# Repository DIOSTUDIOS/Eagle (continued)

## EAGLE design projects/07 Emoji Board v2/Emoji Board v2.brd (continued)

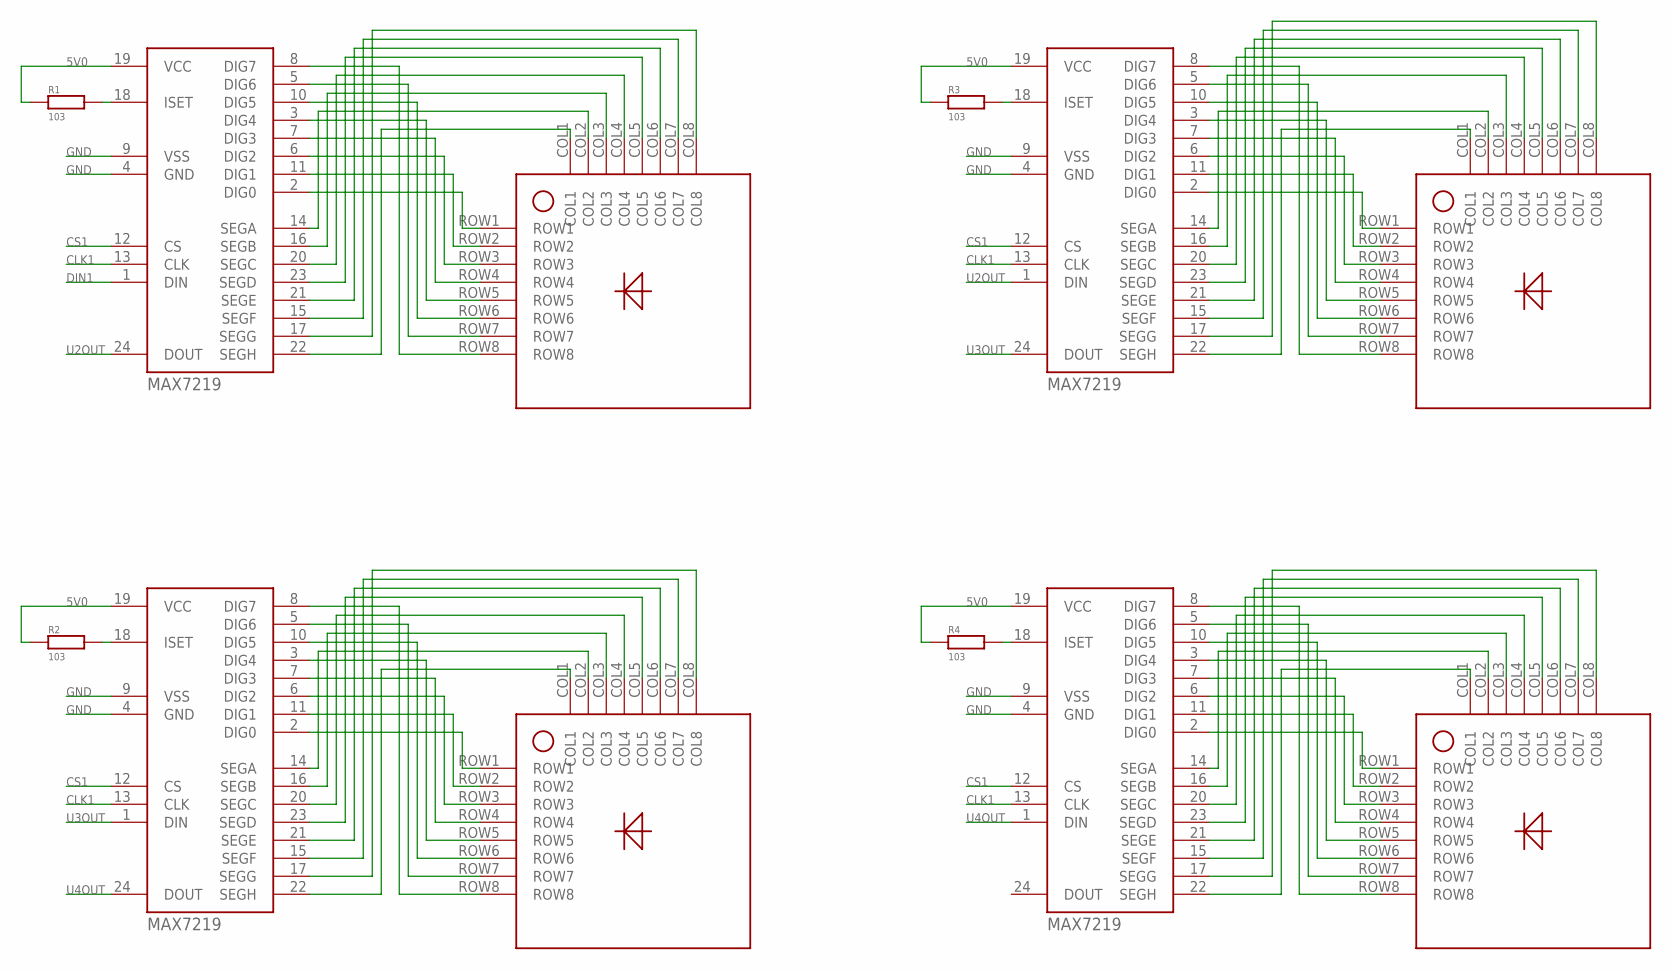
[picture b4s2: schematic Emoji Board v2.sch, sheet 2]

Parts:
R1, R2, R3, R4: 103; R0805
T1, T2, T3, T4: DOT-MATRIX-AS; 1088AS
U2, U3, U4, U5: MAX7219; SOP24

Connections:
5V0: R1.1, R2.1, R3.1, R4.1, U2.19 (VCC), U3.19 (VCC), U4.19 (VCC), U5.19 (VCC); also elsewhere on the board
CLK1: U2.13 (CLK), U3.13 (CLK), U4.13 (CLK), U5.13 (CLK); also elsewhere on the board
CS1: U2.12 (CS), U3.12 (CS), U4.12 (CS), U5.12 (CS); also elsewhere on the board
DIN1: U2.1 (DIN); also elsewhere on the board
GND: U2.4 (GND), U2.9 (VSS), U3.4 (GND), U3.9 (VSS), U4.4 (GND), U4.9 (VSS), U5.4 (GND), U5.9 (VSS); also elsewhere on the board
unnamed: T1.ROW1, U2.2 (DIG0)
unnamed: T1.ROW2, U2.11 (DIG1)
unnamed: T1.ROW3, U2.6 (DIG2)
unnamed: T1.ROW4, U2.7 (DIG3)
unnamed: T1.ROW5, U2.3 (DIG4)
unnamed: T1.ROW6, U2.10 (DIG5)
unnamed: T1.ROW7, U2.5 (DIG6)
unnamed: T1.ROW8, U2.8 (DIG7)
unnamed: T1.COL1, U2.22 (SEGH)
unnamed: T1.COL2, U2.14 (SEGA)
unnamed: T1.COL3, U2.16 (SEGB)
unnamed: T1.COL4, U2.20 (SEGC)
unnamed: T1.COL5, U2.23 (SEGD)
unnamed: T1.COL6, U2.21 (SEGE)
unnamed: T1.COL7, U2.15 (SEGF)
unnamed: T1.COL8, U2.17 (SEGG)
unnamed: T2.ROW1, U3.2 (DIG0)
unnamed: T2.ROW2, U3.11 (DIG1)
unnamed: T2.ROW3, U3.6 (DIG2)
unnamed: T2.ROW4, U3.7 (DIG3)
unnamed: T2.ROW5, U3.3 (DIG4)
unnamed: T2.ROW6, U3.10 (DIG5)
unnamed: T2.ROW7, U3.5 (DIG6)
unnamed: T2.ROW8, U3.8 (DIG7)
unnamed: T2.COL1, U3.22 (SEGH)
unnamed: T2.COL2, U3.14 (SEGA)
unnamed: T2.COL3, U3.16 (SEGB)
unnamed: T2.COL4, U3.20 (SEGC)
unnamed: T2.COL5, U3.23 (SEGD)
unnamed: T2.COL6, U3.21 (SEGE)
unnamed: T2.COL7, U3.15 (SEGF)
unnamed: T2.COL8, U3.17 (SEGG)
unnamed: T3.ROW1, U4.2 (DIG0)
unnamed: T3.ROW2, U4.11 (DIG1)
unnamed: T3.ROW3, U4.6 (DIG2)
unnamed: T3.ROW4, U4.7 (DIG3)
unnamed: T3.ROW5, U4.3 (DIG4)
unnamed: T3.ROW6, U4.10 (DIG5)
unnamed: T3.ROW7, U4.5 (DIG6)
unnamed: T3.ROW8, U4.8 (DIG7)
unnamed: T3.COL1, U4.22 (SEGH)
unnamed: T3.COL2, U4.14 (SEGA)
unnamed: T3.COL3, U4.16 (SEGB)
unnamed: T3.COL4, U4.20 (SEGC)
unnamed: T3.COL5, U4.23 (SEGD)
unnamed: T3.COL6, U4.21 (SEGE)
unnamed: T3.COL7, U4.15 (SEGF)
unnamed: T3.COL8, U4.17 (SEGG)
unnamed: T4.ROW1, U5.2 (DIG0)
unnamed: T4.ROW2, U5.11 (DIG1)
unnamed: T4.ROW3, U5.6 (DIG2)
unnamed: T4.ROW4, U5.7 (DIG3)
unnamed: T4.ROW5, U5.3 (DIG4)
unnamed: T4.ROW6, U5.10 (DIG5)
unnamed: T4.ROW7, U5.5 (DIG6)
unnamed: T4.ROW8, U5.8 (DIG7)
unnamed: T4.COL1, U5.22 (SEGH)
unnamed: T4.COL2, U5.14 (SEGA)
unnamed: T4.COL3, U5.16 (SEGB)
unnamed: T4.COL4, U5.20 (SEGC)
unnamed: T4.COL5, U5.23 (SEGD)
unnamed: T4.COL6, U5.21 (SEGE)
unnamed: T4.COL7, U5.15 (SEGF)
unnamed: T4.COL8, U5.17 (SEGG)
unnamed: R1.2, U2.18 (ISET)
unnamed: R2.2, U4.18 (ISET)
unnamed: R3.2, U3.18 (ISET)
unnamed: R4.2, U5.18 (ISET)
U2OUT: U2.24 (DOUT), U3.1 (DIN)
U3OUT: U3.24 (DOUT), U4.1 (DIN)
U4OUT: U4.24 (DOUT), U5.1 (DIN)

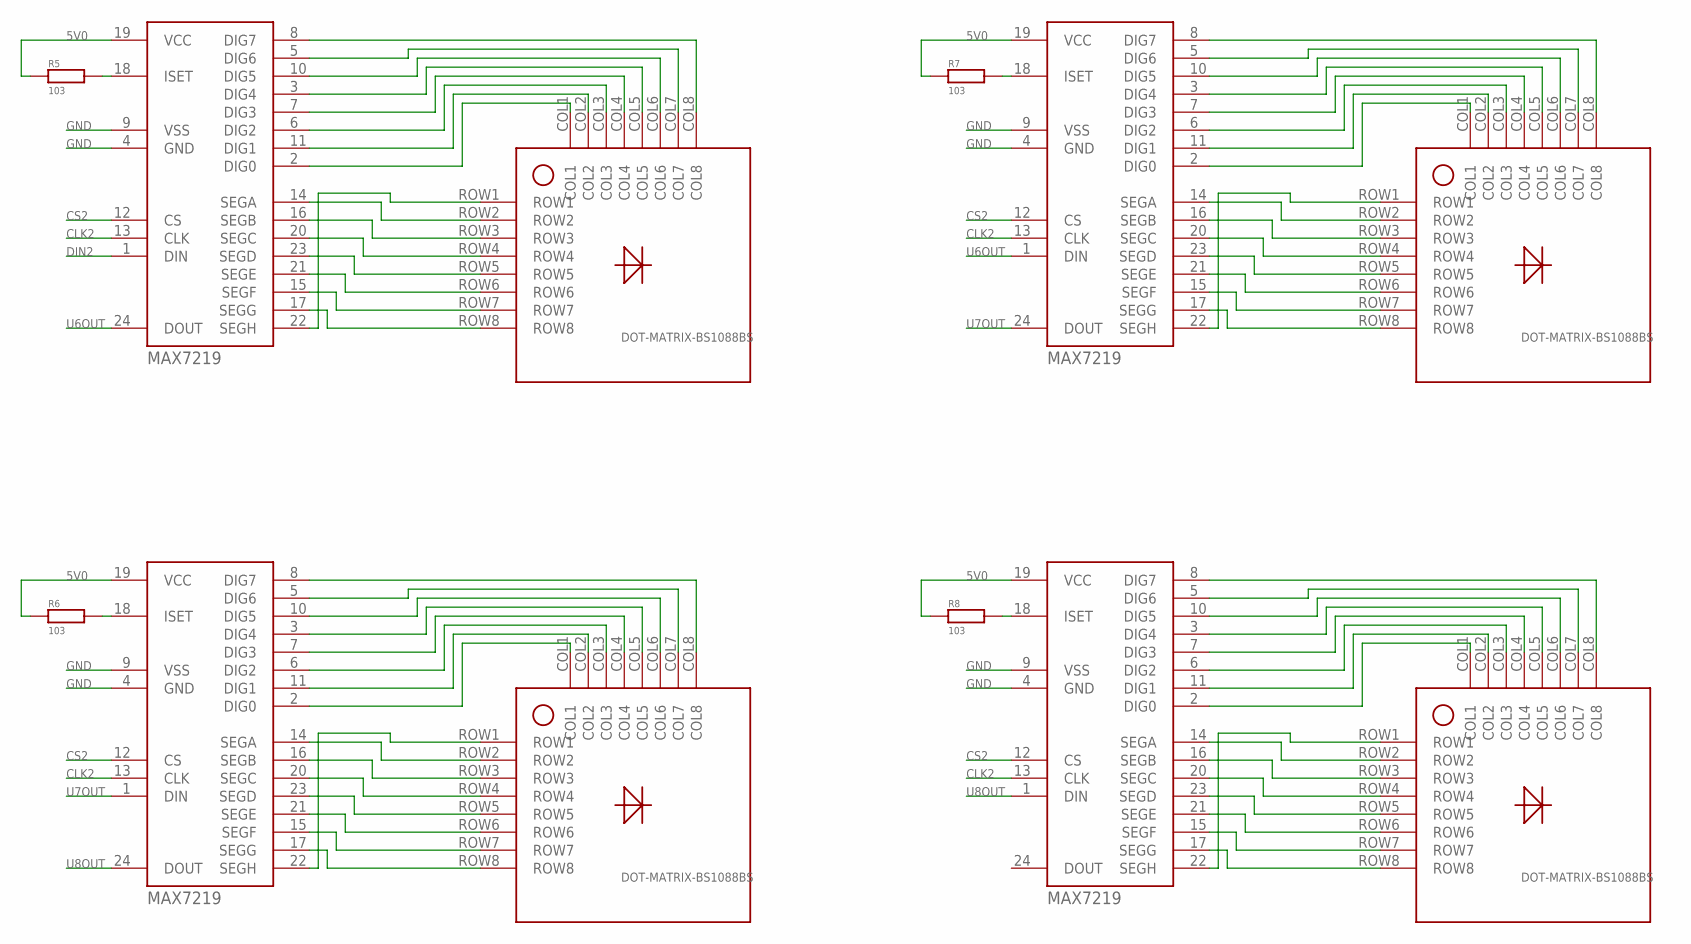
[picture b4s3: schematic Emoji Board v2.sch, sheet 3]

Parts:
R5, R6, R7, R8: 103; R0805
T5, T6, T7, T8: DOT-MATRIX-BS1088BS; 1088BS
U6, U7, U8, U9: MAX7219; SOP24

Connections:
5V0: R5.1, R6.1, R7.1, R8.1, U6.19 (VCC), U7.19 (VCC), U8.19 (VCC), U9.19 (VCC); also elsewhere on the board
CLK2: U6.13 (CLK), U7.13 (CLK), U8.13 (CLK), U9.13 (CLK); also elsewhere on the board
CS2: U6.12 (CS), U7.12 (CS), U8.12 (CS), U9.12 (CS); also elsewhere on the board
DIN2: U6.1 (DIN); also elsewhere on the board
GND: U6.4 (GND), U6.9 (VSS), U7.4 (GND), U7.9 (VSS), U8.4 (GND), U8.9 (VSS), U9.4 (GND), U9.9 (VSS); also elsewhere on the board
unnamed: R5.2, U6.18 (ISET)
unnamed: R6.2, U8.18 (ISET)
unnamed: T5.ROW8, U6.17 (SEGG)
unnamed: T5.ROW7, U6.15 (SEGF)
unnamed: T5.ROW6, U6.21 (SEGE)
unnamed: T5.ROW5, U6.23 (SEGD)
unnamed: T5.ROW4, U6.20 (SEGC)
unnamed: T5.ROW3, U6.16 (SEGB)
unnamed: T5.ROW2, U6.14 (SEGA)
unnamed: T5.ROW1, U6.22 (SEGH)
unnamed: T5.COL1, U6.2 (DIG0)
unnamed: T5.COL2, U6.11 (DIG1)
unnamed: T5.COL3, U6.6 (DIG2)
unnamed: T5.COL4, U6.7 (DIG3)
unnamed: T5.COL5, U6.3 (DIG4)
unnamed: T5.COL6, U6.10 (DIG5)
unnamed: T5.COL7, U6.5 (DIG6)
unnamed: T5.COL8, U6.8 (DIG7)
unnamed: T6.ROW8, U7.17 (SEGG)
unnamed: T6.ROW7, U7.15 (SEGF)
unnamed: T6.ROW6, U7.21 (SEGE)
unnamed: T6.ROW5, U7.23 (SEGD)
unnamed: T6.ROW4, U7.20 (SEGC)
unnamed: T6.ROW3, U7.16 (SEGB)
unnamed: T6.ROW2, U7.14 (SEGA)
unnamed: T6.ROW1, U7.22 (SEGH)
unnamed: T6.COL1, U7.2 (DIG0)
unnamed: T6.COL2, U7.11 (DIG1)
unnamed: T6.COL3, U7.6 (DIG2)
unnamed: T6.COL4, U7.7 (DIG3)
unnamed: T6.COL5, U7.3 (DIG4)
unnamed: T6.COL6, U7.10 (DIG5)
unnamed: T6.COL7, U7.5 (DIG6)
unnamed: T6.COL8, U7.8 (DIG7)
unnamed: T8.ROW8, U9.17 (SEGG)
unnamed: T8.ROW7, U9.15 (SEGF)
unnamed: T8.ROW6, U9.21 (SEGE)
unnamed: T8.ROW5, U9.23 (SEGD)
unnamed: T8.ROW4, U9.20 (SEGC)
unnamed: T8.ROW3, U9.16 (SEGB)
unnamed: T8.ROW2, U9.14 (SEGA)
unnamed: T8.ROW1, U9.22 (SEGH)
unnamed: T8.COL1, U9.2 (DIG0)
unnamed: T8.COL2, U9.11 (DIG1)
unnamed: T8.COL3, U9.6 (DIG2)
unnamed: T8.COL4, U9.7 (DIG3)
unnamed: T8.COL5, U9.3 (DIG4)
unnamed: T8.COL6, U9.10 (DIG5)
unnamed: T8.COL7, U9.5 (DIG6)
unnamed: T8.COL8, U9.8 (DIG7)
unnamed: T7.ROW8, U8.17 (SEGG)
unnamed: T7.ROW7, U8.15 (SEGF)
unnamed: T7.ROW6, U8.21 (SEGE)
unnamed: T7.ROW5, U8.23 (SEGD)
unnamed: T7.ROW4, U8.20 (SEGC)
unnamed: T7.ROW3, U8.16 (SEGB)
unnamed: T7.ROW2, U8.14 (SEGA)
unnamed: T7.ROW1, U8.22 (SEGH)
unnamed: T7.COL1, U8.2 (DIG0)
unnamed: T7.COL2, U8.11 (DIG1)
unnamed: T7.COL3, U8.6 (DIG2)
unnamed: T7.COL4, U8.7 (DIG3)
unnamed: T7.COL5, U8.3 (DIG4)
unnamed: T7.COL6, U8.10 (DIG5)
unnamed: T7.COL7, U8.5 (DIG6)
unnamed: T7.COL8, U8.8 (DIG7)
unnamed: R7.2, U7.18 (ISET)
unnamed: R8.2, U9.18 (ISET)
U6OUT: U6.24 (DOUT), U7.1 (DIN)
U7OUT: U7.24 (DOUT), U8.1 (DIN)
U8OUT: U8.24 (DOUT), U9.1 (DIN)

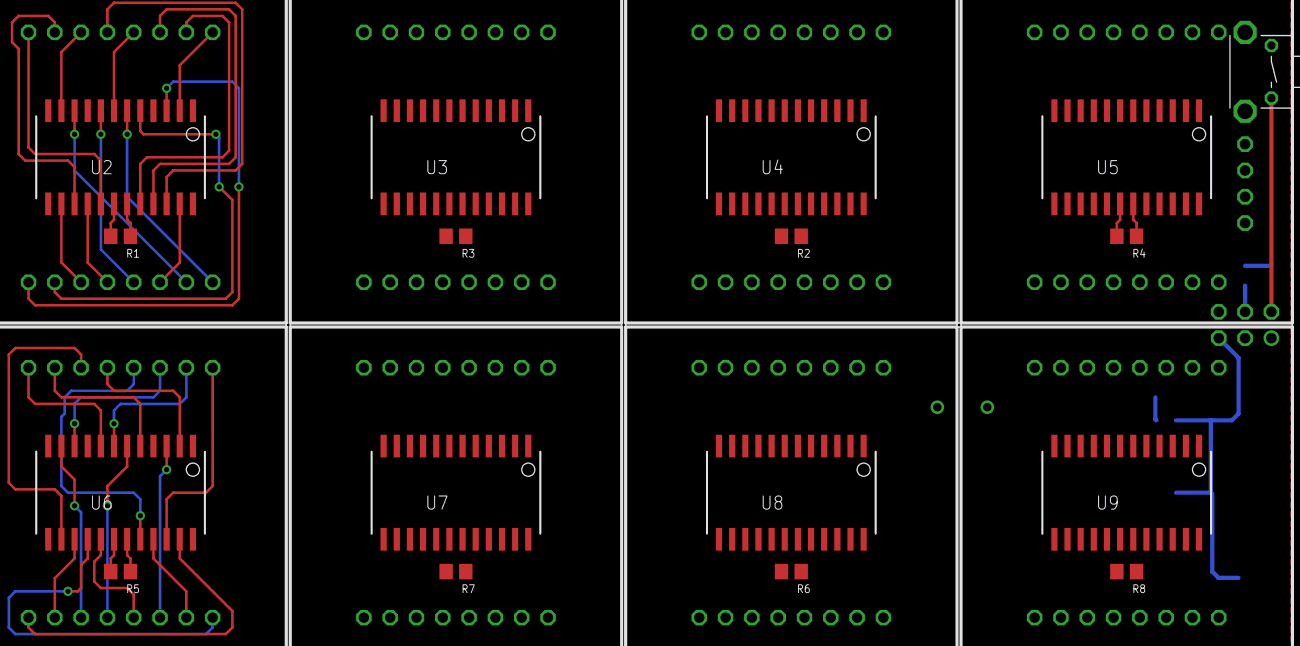
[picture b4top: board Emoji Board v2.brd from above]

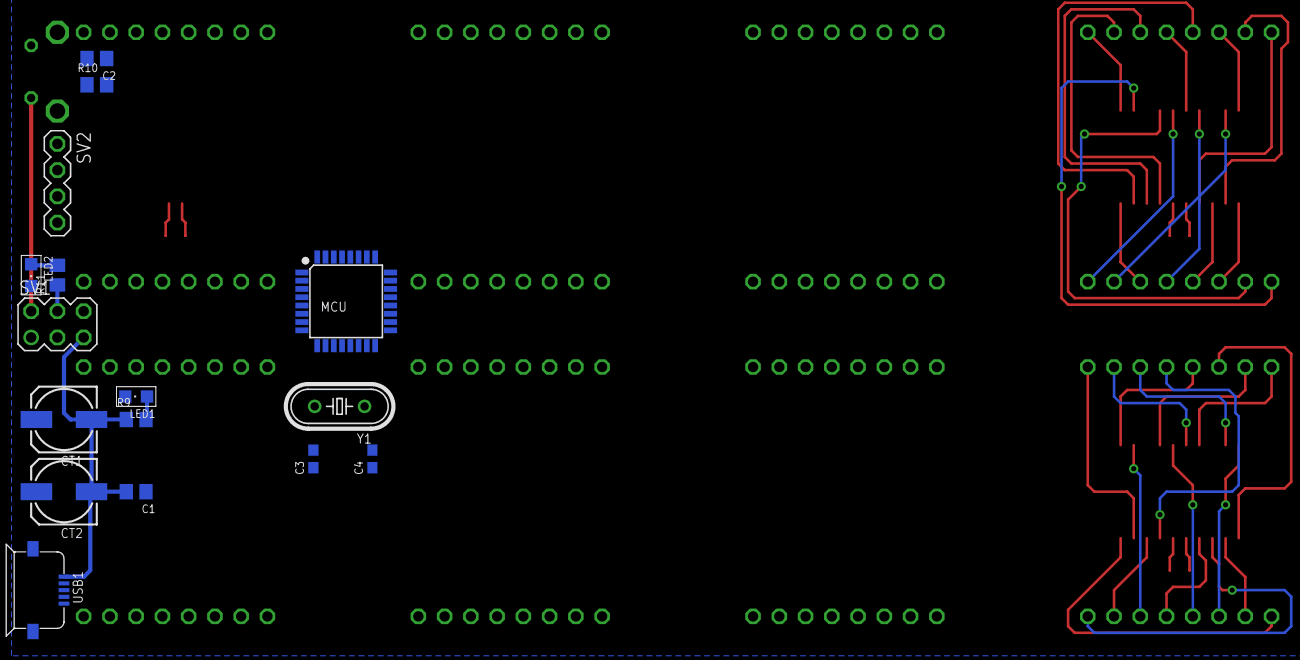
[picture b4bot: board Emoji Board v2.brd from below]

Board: 2 copper layers, 41 parts (16 on the bottom side), 160 nets.
